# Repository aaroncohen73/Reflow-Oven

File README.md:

# Code and Design files for Solder Reflow Toaster Oven

The code (available inside `code/`) is licensed under the
[GNU General Public License, version 3](https://www.gnu.org/licenses/gpl.html), and
the PCB design (available inside `design/`) is licensed under the
[Creative Commons ShareAlike 4.0 International](https://creativecommons.org/licenses/by-sa/4.0/) license.

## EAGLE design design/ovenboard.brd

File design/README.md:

# EAGLE CAD Design Files for Solder Reflow Toaster Oven

This design is compatible with EAGLE 8.2+

This design is licensed under the [Creative Commons ShareAlike 4.0 International](https://creativecommons.org/licenses/by-sa/4.0/) license.

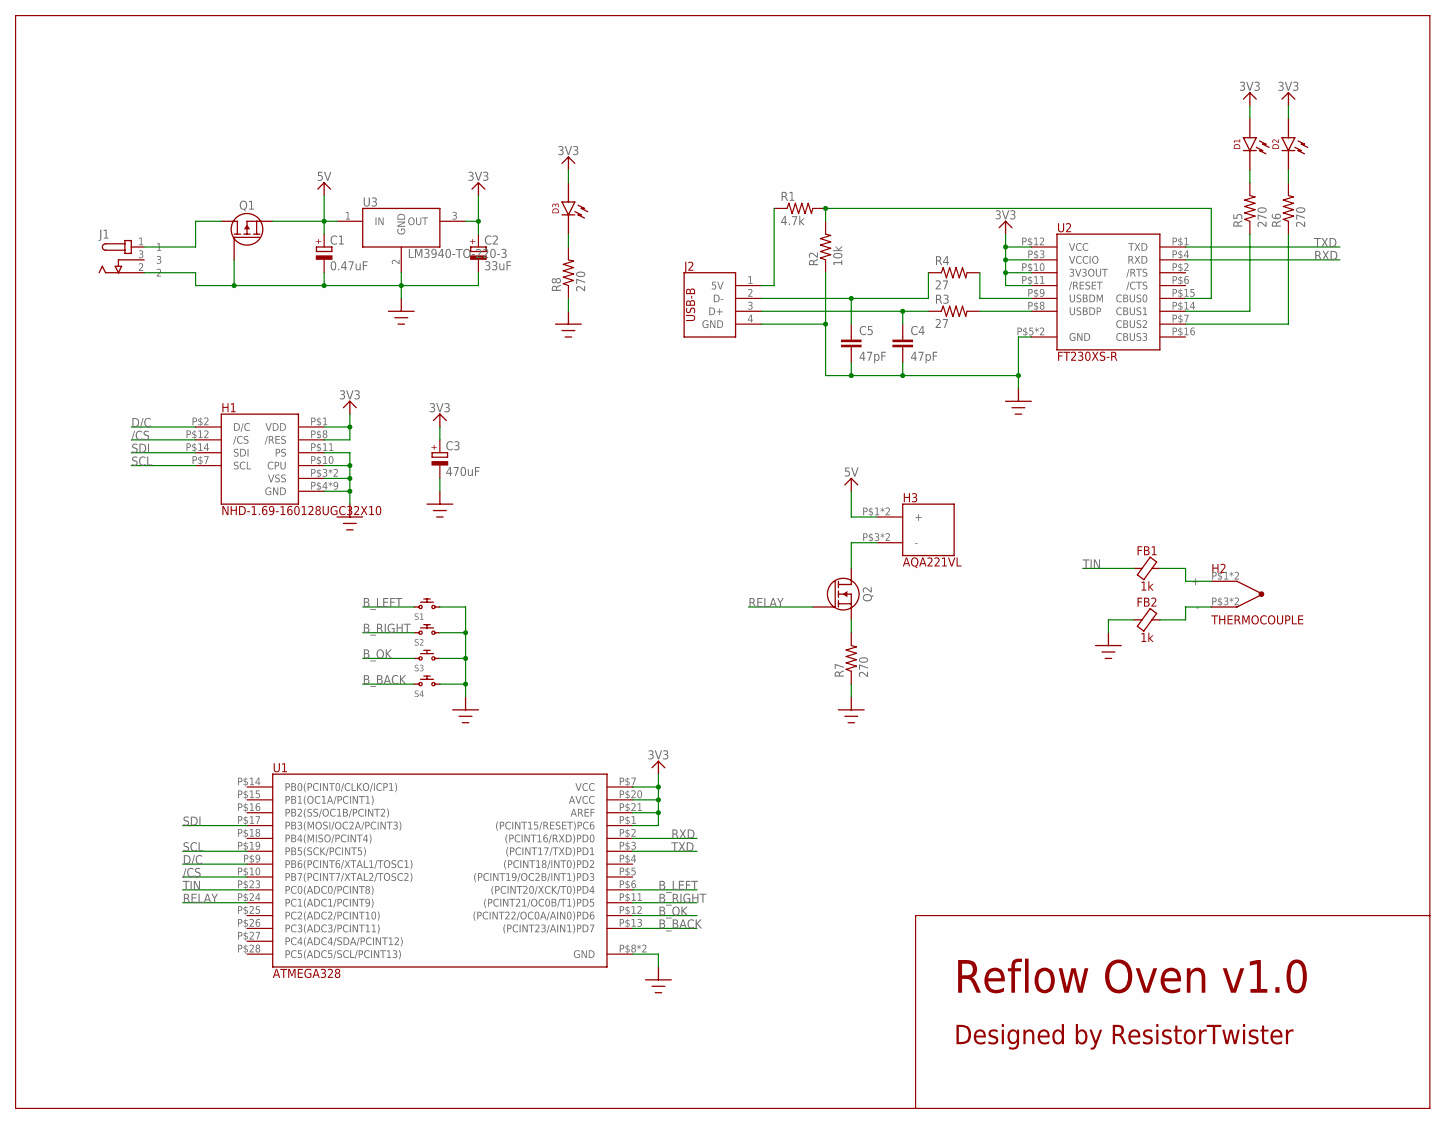
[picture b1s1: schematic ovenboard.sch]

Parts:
C1: 0.47uF; E5-5
C2: 33uF; E5-5
C3: 470uF; E5-5
C4, C5: 47pF; C050-024X044
D1, D2, D3: LED-5; LED5
FB1, FB2: 1k; 0603
H1: NHD-1.69-160128UGC32X10; 2X10HEADER0.1
H2: THERMOCOUPLE; 2TERMINAL
H3: AQA221VL; 2TERMINAL
J1: PJ-202B
J2: USB2.0-B1HSW6; B1HSW6
Q1: MOSFET-P-TO-220-3; TO-220-3
Q2: MOSFET-N-TO-92; TO-92
R1: 4.7k; 0204/5
R2: 10k; 0204/5
R3, R4: 27; 0204/5
R5, R6, R7, R8: 270; 0204/5
S1, S2, S3, S4: PUSHBUTTON; 1X2HEADER0.1
U1: ATMEGA328; 28DIP0.1
U2: FT230XS-R; 16SSOP0.025
U3: LM3940-TO-220-3; TO-220-3

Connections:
3V3: C2.+, C3.+, D1.A, D2.A, D3.A, H1.P$1 (VDD), H1.P$8 (/RES), U1.P$1 ((PCINT15/RESET)PC6), U1.P$7 (VCC), U1.P$20 (AVCC), U1.P$21 (AREF), U2.P$3 (VCCIO), U2.P$10 (3V3OUT), U2.P$11 (/RESET), U2.P$12 (VCC), U3.3 (OUT)
5V: C1.+, H3.P$1 (+), H3.P$2 (+), Q1.2 (S), U3.1 (IN)
/CS: H1.P$12 (/CS), U1.P$10 (PB7(PCINT7/XTAL2/TOSC2))
B_BACK: S4.2, U1.P$13 ((PCINT23/AIN1)PD7)
B_LEFT: S1.2, U1.P$6 ((PCINT20/XCK/T0)PD4)
B_OK: S3.2, U1.P$12 ((PCINT22/OC0A/AIN0)PD6)
B_RIGHT: S2.2, U1.P$11 ((PCINT21/OC0B/T1)PD5)
D/C: H1.P$2 (D/C), U1.P$9 (PB6(PCINT6/XTAL1/TOSC1))
GND: C1.-, C2.-, C3.-, C4.2, C5.2, FB2.1, H1.P$3 (VSS), H1.P$4 (GND), H1.P$5 (GND), H1.P$6 (GND), H1.P$9 (GND), H1.P$10 (CPU), H1.P$11 (PS), H1.P$13 (GND), H1.P$15 (GND), H1.P$16 (GND), H1.P$17 (GND), H1.P$18 (VSS), H1.P$20 (GND), J1.2, J2.4 (GND), Q1.1 (G), R2.1, R7.1, R8.1, S1.1, S2.1, S3.1, S4.1, U1.P$8 (GND), U1.P$22 (GND), U2.P$5 (GND), U2.P$13 (GND), U3.2 (GND)
unnamed: J1.1, Q1.3 (D)
unnamed: R3.2, U2.P$8 (USBDP)
unnamed: C5.1, J2.2 (D-), R4.1
unnamed: C4.1, J2.3 (D+), R3.1
unnamed: J2.1 (5V), R1.1
unnamed: R1.2, R2.2, U2.P$15 (CBUS0)
unnamed: R5.1, U2.P$14 (CBUS1)
unnamed: R6.1, U2.P$7 (CBUS2)
unnamed: R4.2, U2.P$9 (USBDM)
unnamed: D1.C, R5.2
unnamed: D2.C, R6.2
unnamed: FB1.2, H2.P$1 (+), H2.P$2 (+)
unnamed: FB2.2, H2.P$3 (-), H2.P$4 (-)
unnamed: H3.P$3 (-), H3.P$4 (-), Q2.3 (D)
unnamed: D3.C, R8.2
unnamed: Q2.1 (S), R7.2
RELAY: Q2.2 (G), U1.P$24 (PC1(ADC1/PCINT9))
RXD: U1.P$2 ((PCINT16/RXD)PD0), U2.P$4 (RXD)
SCL: H1.P$7 (SCL), U1.P$19 (PB5(SCK/PCINT5))
SDI: H1.P$14 (SDI), U1.P$17 (PB3(MOSI/OC2A/PCINT3))
TIN: FB1.1, U1.P$23 (PC0(ADC0/PCINT8))
TXD: U1.P$3 ((PCINT17/TXD)PD1), U2.P$1 (TXD)

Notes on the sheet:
Reflow Oven v1.0
Designed by ResistorTwister

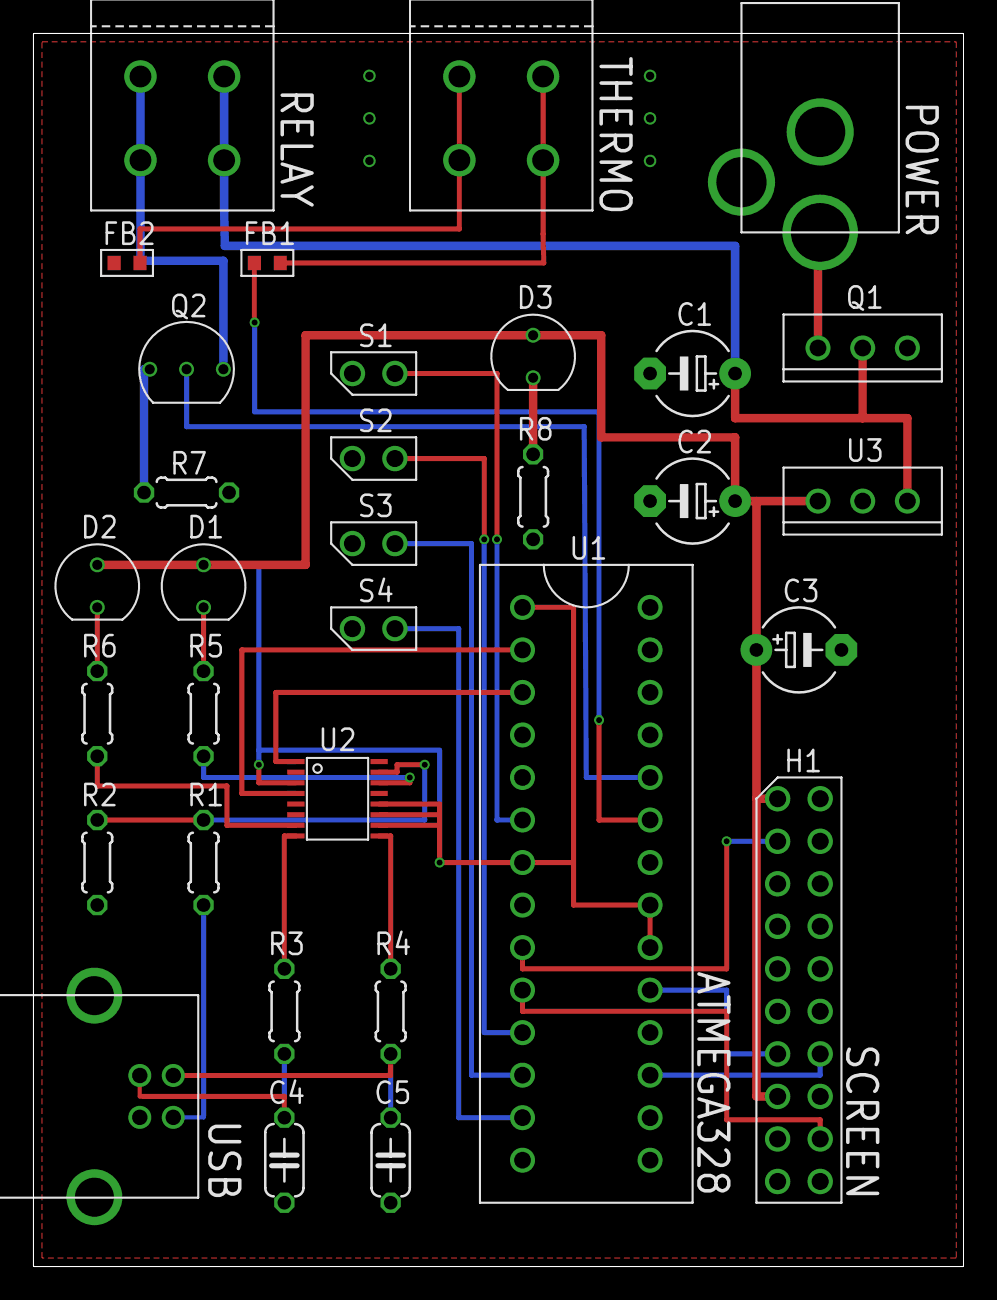
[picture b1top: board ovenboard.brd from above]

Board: 2 copper layers, 55.5 x 73.7 mm, 32 parts (0 on the bottom side), 31 nets.

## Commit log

2017-08-14 Design and board layout
2017-09-12 Add FontTool and SPI interface
2017-09-20 README files and simple bootloader
